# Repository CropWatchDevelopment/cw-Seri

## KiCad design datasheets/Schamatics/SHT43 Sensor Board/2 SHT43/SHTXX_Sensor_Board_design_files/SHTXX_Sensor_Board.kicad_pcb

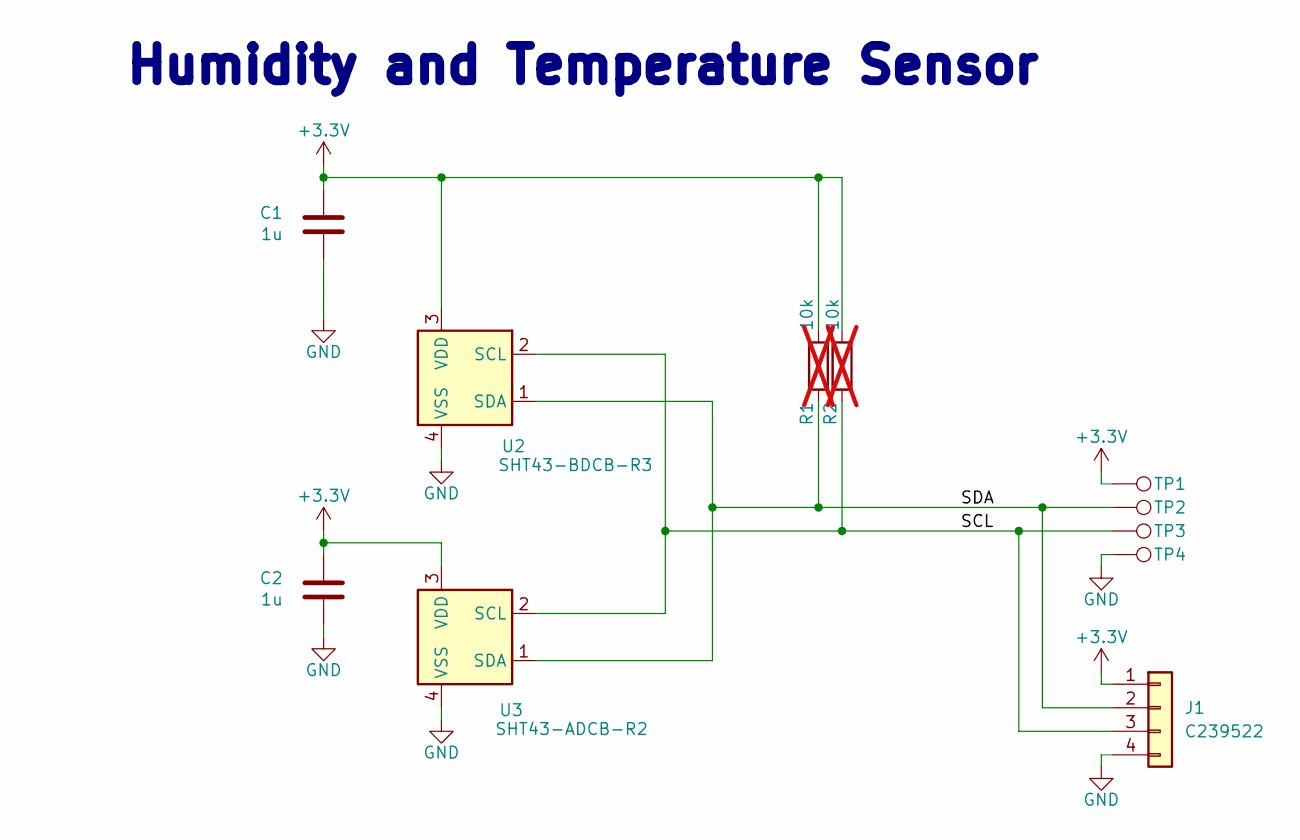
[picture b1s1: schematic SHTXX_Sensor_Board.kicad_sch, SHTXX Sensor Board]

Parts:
C1, C2: 1u; C_0402_1005Metric; Voltage Rating 10V; MPN CL05A105KP5NNNC; LCSC Part # CL05A105KP5NNNC
J1: C239522; SM04B-SRSS-TB_LFSN_; MPN A1002WR-S-4P; LCSC Part # C239522
R1, R2: 10k; R_0402_1005Metric; MPN AC0402FR-0710KL; not fitted
TP1, TP2, TP3, TP4: TestPoint; TestPoint_Pad_D2.0mm
U2: SHT43-BDCB-R3; Sensirion_DFN-4_1.5x1.5mm_P0.8mm_SHT4x_NoCentralPad
U3: SHT43-ADCB-R2; Sensirion_DFN-4_1.5x1.5mm_P0.8mm_SHT4x_NoCentralPad

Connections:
+3.3V: C1.1, C2.1, J1.1, R1.2, R2.2, TP1.1, U2.3 (VDD), U3.3 (VDD)
/SCL: J1.3, R2.1, TP3.1, U2.2 (SCL), U3.2 (SCL)
/SDA: J1.2, R1.1, TP2.1, U2.1 (SDA), U3.1 (SDA)
GND: C1.2, C2.2, J1.4, TP4.1, U2.4 (VSS), U3.4 (VSS)

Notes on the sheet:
Humidity and Temperature Sensor

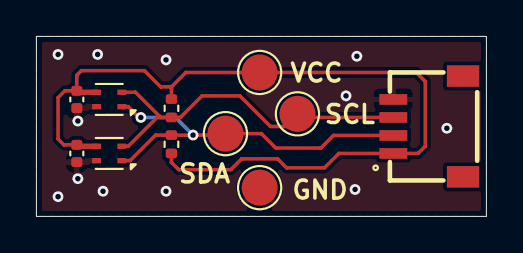
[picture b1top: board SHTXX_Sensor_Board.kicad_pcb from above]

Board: 2 copper layers, 25.0 x 10.0 mm, 11 parts (0 on the bottom side), 4 nets.

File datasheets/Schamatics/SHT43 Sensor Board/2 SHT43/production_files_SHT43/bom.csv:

Designator,Footprint,Quantity,Value,LCSC Part #
"C1, C2",0402,2,1u,CL05A105KP5NNNC 
J1,SM04B-SRSS-TB_LFSN_,1,C239522,C239522
U2,Sensirion_DFN-4_1.5x1.5mm_P0.8mm_SHT4x_NoCentralPad,1,SHT43-BDCB-R3,
U3,Sensirion_DFN-4_1.5x1.5mm_P0.8mm_SHT4x_NoCentralPad,1,SHT43-ADCB-R2,

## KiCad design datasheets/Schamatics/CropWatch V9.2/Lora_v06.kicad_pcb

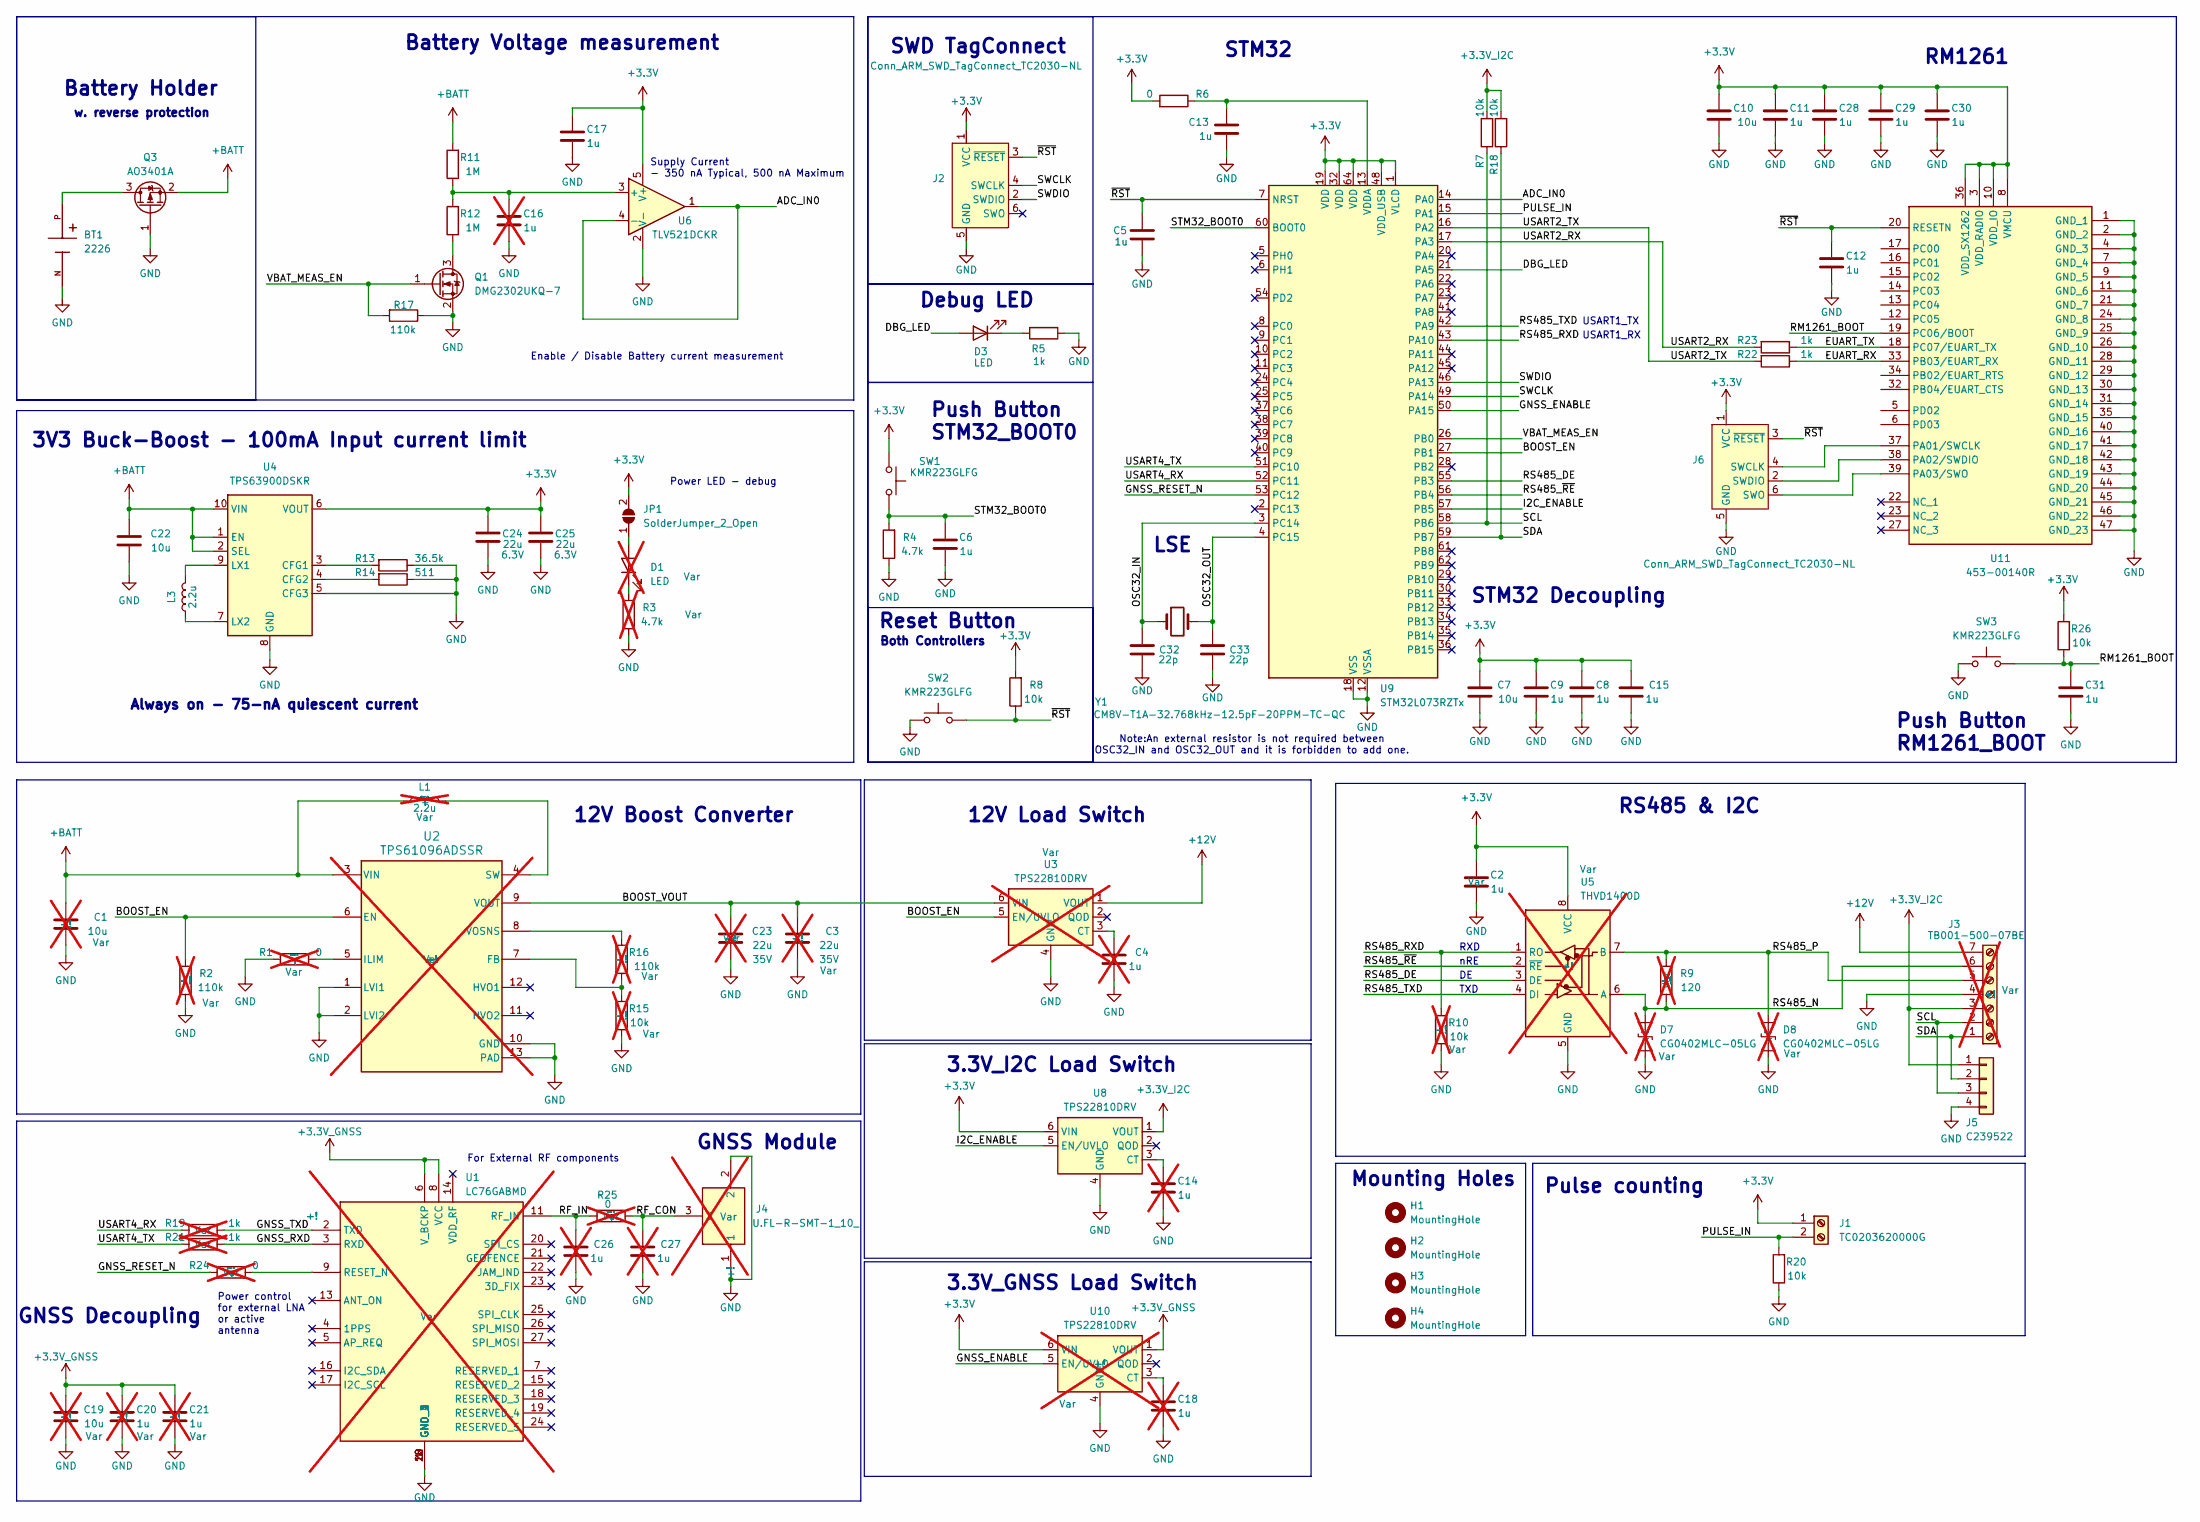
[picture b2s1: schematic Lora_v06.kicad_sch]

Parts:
BT1: 2226; BAT_2226; PARTREV 6.22.07
C1, C19: 10u; C_0603_1608Metric; Voltage Rating 10V; MPN GRM188R61A106ME69J; not fitted
C2, C5, C6, C8, C9, C11, C12, C13, C15, C17, C28, C29, C30, C31: 1u; C_0402_1005Metric; Voltage Rating 10V; MPN CL05A105KP5NNNC
C3, C23: 22u; C_0805_2012Metric; Voltage Rating 35V; MPN C2012X5R1V226M125AC; not fitted
C4, C14, C16, C18, C20, C21, C26, C27: 1u; C_0402_1005Metric; Voltage Rating 10V; MPN CL05A105KP5NNNC; not fitted
C7, C10, C22: 10u; C_0603_1608Metric; Voltage Rating 10V; MPN GRM188R61A106ME69J
C24, C25: 22u; C_0603_1608Metric; Voltage Rating 6.3V; MPN GRM188R60J226MEA0J
C32, C33: 22p; C_0402_1005Metric; Voltage Rating 50V; MPN GRM1555C1H220JA01J
D1: LED; LED_0402_1005Metric; MPN QBLP595-IG; not fitted
D3: LED; LED_0402_1005Metric; MPN QBLP595-IG
D7, D8: CG0402MLC-05LG; D_0402_1005Metric; MPN CG0402MLC-05LG; not fitted
H1, H2, H3, H4: MountingHole; MountingHole_4.3mm_M4
J1: TC0203620000G; MPN TC0203620000G
J2, J6: Conn_ARM_SWD_TagConnect_TC2030-NL; Tag-Connect_TC2030-IDC-NL_2x03_P1.27mm_Vertical
J3: TB001-500-07BE; CUI_TB001-500-07BE; MPN TB001-500-07BE; not fitted
J4: U.FL-R-SMT-1_10_; Mouser Part Number 798-U.FL-R-SMT-110; not fitted
J5: C239522; SM04B-SRSS-TB_LFSN_; MPN A1002WR-S-4P; LCSC Part # C239522
JP1: SolderJumper_2_Open; SolderJumper-2_P1.3mm_Open_RoundedPad1.0x1.5mm
L1: 2.2u; L_0805_2012Metric; MPN LQM21PN2R2MGHL; not fitted
L3: 2.2u; L_0805_2012Metric; MPN LQM21PN2R2MGHL
Q1: DMG2302UKQ-7; SOT-23; MPN DMG2302UKQ-7
Q3: AO3401A; SOT-23; MPN AO3401A
R1, R24, R25: 0; R_0402_1005Metric; MPN RC0402FR-070RL; not fitted
R2, R16: 110k; R_0402_1005Metric; MPN RC0402FR-07110KL; not fitted
R3: 4.7k; R_0402_1005Metric; MPN CRGCQ0402F4K7; not fitted
R4: 4.7k; R_0402_1005Metric; MPN CRGCQ0402F4K7
R5, R22, R23: 1k; R_0402_1005Metric; MPN WR04X1001FTL
R6: 0; R_0402_1005Metric; MPN RC0402FR-070RL
R7, R8, R18, R20, R26: 10k; R_0402_1005Metric; MPN AC0402FR-0710KL
R9: 120; R_0402_1005Metric; MPN RC0402FR-07120RL; not fitted
R10, R15: 10k; R_0402_1005Metric; MPN AC0402FR-0710KL; not fitted
R11, R12: 1M; R_0402_1005Metric; MPN CRGCQ0402F1M0
R13: 36.5k; R_0402_1005Metric; MPN RC0402FR-0736K5L
R14: 511; R_0402_1005Metric; MPN RC0402FR-07511RL
R17: 110k; R_0402_1005Metric; MPN RC0402FR-07110KL
R19, R21: 1k; R_0402_1005Metric; MPN WR04X1001FTL; not fitted
SW1, SW2, SW3: KMR223GLFG; SW_Push_1P1T-SH_NO_CK_KMR2xxG; MPN KMR223GLFG
U1: LC76GABMD; Mouser Part Number 277-LC76GABMD; not fitted
U2: TPS61096ADSSR; DSS0012A; MPN TPS61096ADSSR; not fitted
U3, U10: TPS22810DRV; WSON-6-1EP_2x2mm_P0.65mm_EP1x1.6mm; MPN TPS22810DRVR; not fitted
U4: TPS63900DSKR; WSON-10-1EP_2.5x2.5mm_P0.5mm_EP1.2x2mm_ThermalVias; MPN TPS63900DSKR
U5: THVD1400D; SOIC-8_3.9x4.9mm_P1.27mm; MPN THVD1400DR; not fitted
U6: TLV521DCKR; SOT65P210X110-5N; MPN TLV521DCKR
U8: TPS22810DRV; WSON-6-1EP_2x2mm_P0.65mm_EP1x1.6mm; MPN TPS22810DRVR
U9: STM32L073RZTx; LQFP-64_10x10mm_P0.5mm; MPN STM32L073RZT6
U11: 453-00140R; 45300140R; Mouser Part Number 239-453-00140R
Y1: CM8V-T1A-32.768kHz-12.5pF-20PPM-TC-QC; CM8V32768TA020125

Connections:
+3.3V: C2.1, C7.1, C8.1, C9.1, C10.1, C11.1, C15.1, C17.1, C24.1, C25.1, C28.1, C29.1, C30.1, J1.1, J2.1 (VCC), J6.1 (VCC), JP1.2 (B), R6.2, R8.2, R26.2, SW1.1, U4.6 (VOUT), U5.8 (VCC), U6.5 (V+), U8.6 (VIN), U9.1 (VLCD), U9.19 (VDD), U9.32 (VDD), U9.48 (VDD_USB), U9.64 (VDD), U10.6 (VIN), U11.3 (VDD_RADIO), U11.8 (VMCU), U11.10 (VDD_IO), U11.36 (VDD_SX1262)
+3.3V_GNSS: C19.1, C20.1, C21.1, U1.6 (V_BCKP), U1.8 (VCC), U10.1 (VOUT)
+3.3V_I2C: J3.3, J5.1, R7.2, R18.2, U8.1 (VOUT)
+12V: J3.7, U3.1 (VOUT)
+BATT: C1.1, C22.1, L1.1, Q3.2 (S), R11.2, U2.3 (VIN), U4.1 (EN), U4.2 (SEL), U4.10 (VIN)
/ADC_IN0: U6.1, U6.4 (-), U9.14 (PA0)
/BOOST_EN: R2.2, U2.6 (EN), U3.5 (EN/UVLO), U9.27 (PB1)
/BOOST_VOUT: C3.1, C23.1, U2.9 (VOUT), U3.6 (VIN)
/DBG_LED: D3.2 (A), U9.21 (PA5)
/EUART_RX: R22.1, U11.33 (PB03/EUART_RX)
/EUART_TX: R23.1, U11.18 (PC07/EUART_TX)
/GNSS_ENABLE: U9.50 (PA15), U10.5 (EN/UVLO)
/GNSS_RESET_N: R24.1, U9.53 (PC12)
/GNSS_RXD: R21.1, U1.3 (RXD)
/GNSS_TXD: R19.1, U1.2 (TXD)
/I2C_ENABLE: U8.5 (EN/UVLO), U9.57 (PB5)
/OSC32_IN: C32.1, U9.3 (PC14), Y1.1
/OSC32_OUT: C33.1, U9.4 (PC15), Y1.2
/PULSE_IN: J1.2, R20.2, U9.15 (PA1)
/RF_CON: C27.1, J4.3, R25.2
/RF_IN: C26.1, R25.1, U1.11 (RF_IN)
/RM1261_BOOT: C31.1, R26.1, SW3.2, U11.19 (PC06/BOOT)
/RS485_DE: U5.3 (DE), U9.55 (PB3)
/RS485_N: D7.2 (A2), J3.6, R9.1, U5.6 (A)
/RS485_P: D8.2 (A2), J3.5, R9.2, U5.7 (B)
/RS485_RXD: R10.2, U5.1 (RO), U9.43 (PA10)
/RS485_TXD: U5.4 (DI), U9.42 (PA9)
/RS485_~RE: U5.2 (~RE), U9.56 (PB4)
/SCL: J3.2, J5.3, R7.1, U9.58 (PB6)
/SDA: J3.1, J5.2, R18.1, U9.59 (PB7)
/STM32_BOOT0: C6.1, R4.2, SW1.2, U9.60 (BOOT0)
/SWCLK: J2.4 (SWCLK), U9.49 (PA14)
/SWDIO: J2.2 (SWDIO), U9.46 (PA13)
/USART2_RX: R23.2, U9.17 (PA3)
/USART2_TX: R22.2, U9.16 (PA2)
/USART4_RX: R19.2, U9.52 (PC11)
/USART4_TX: R21.2, U9.51 (PC10)
/VBAT_MEAS_EN: Q1.1 (G), R17.2, U9.26 (PB0)
/~RST: C5.1, C12.1, J2.3 (~RESET), J6.3 (~RESET), R8.1, SW2.2, U9.7 (NRST), U11.20 (RESETN)
GND: BT1.N, C1.2, C2.2, C3.2, C4.2, C5.2, C6.2, C7.2, C8.2, C9.2, C10.2, C11.2, C12.2, C13.2, C14.2, C15.2, C16.2, C17.2, C18.2, C19.2, C20.2, C21.2, C22.2, C23.2, C24.2, C25.2, C26.2, C27.2, C28.2, C29.2, C30.2, C31.2, C32.2, C33.2, D7.1 (A1), D8.1 (A1), J2.5 (GND), J3.4, J4.1, J4.2, J5.4, J6.5 (GND), Q1.2 (S), Q3.1 (G), R1.1, R2.1, R3.1, R4.1, R5.1, R10.1, R13.1, R14.1, R15.1, R17.1, R20.1, SW2.1, SW3.1, U1.1 (GND_1), U1.10 (GND_2), U1.12 (GND_3), U1.28 (GND_4), U2.1 (LVI1), U2.2 (LVI2), U2.10 (GND), U2.13 (PAD), U3.4 (GND), U3.7 (GND), U4.5 (CFG3), U4.8 (GND), U4.11 (GND), U5.5 (GND), U6.2 (V-), U8.4 (GND), U8.7 (GND), U9.12 (VSSA), U9.18 (VSS), U9.31 (VSS), U9.47 (VSS), U9.63 (VSS), U10.4 (GND), U10.7 (GND), U11.1 (GND_1), U11.2 (GND_2), U11.4 (GND_3), U11.7 (GND_4), U11.9 (GND_5), U11.11 (GND_6), U11.21 (GND_7), U11.24 (GND_8), U11.25 (GND_9), U11.26 (GND_10), U11.28 (GND_11), U11.29 (GND_12), U11.30 (GND_13), U11.31 (GND_14), U11.35 (GND_15), U11.40 (GND_16), U11.41 (GND_17), U11.42 (GND_18), U11.43 (GND_19), U11.44 (GND_20), U11.45 (GND_21), U11.46 (GND_22), U11.47 (GND_23)
unnamed: D1.2 (A), JP1.1 (A)
unnamed: D1.1 (K), R3.2
unnamed: D3.1 (K), R5.2
unnamed: J6.4 (SWCLK), U11.37 (PA01/SWCLK)
unnamed: J6.2 (SWDIO), U11.38 (PA02/SWDIO)
unnamed: J6.6 (SWO), U11.39 (PA03/SWO)
unnamed: Q1.3 (D), R12.1
unnamed: BT1.P, Q3.3 (D)
unnamed: R24.2, U1.9 (RESET_N)
unnamed: R15.2, R16.1, U2.7 (FB)
unnamed: R1.2, U2.5 (ILIM)
unnamed: L1.2, U2.4 (SW)
unnamed: R16.2, U2.8 (VOSNS)
unnamed: C4.1, U3.3 (CT)
unnamed: R13.2, U4.3 (CFG1)
unnamed: R14.2, U4.4 (CFG2)
unnamed: L3.2, U4.9 (LX1)
unnamed: L3.1, U4.7 (LX2)
unnamed: C16.1, R11.1, R12.2, U6.3 (+)
unnamed: C14.1, U8.3 (CT)
unnamed: C13.1, R6.1, U9.13 (VDDA)
unnamed: C18.1, U10.3 (CT)

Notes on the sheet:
STM32
3V3 Buck-Boost - 100mA Input current limit
3.3V_GNSS Load Switch
Push Button STM32_BOOT0
LSE
RM1261
STM32 Decoupling
Push Button RM1261_BOOT
RS485 & I2C
Supply Current - 350 nA Typical, 500 nA Maximum
12V Boost Converter
Both Controllers
SWD TagConnect
Pulse counting
Battery Holder
12V Load Switch
3.3V_I2C Load Switch
Power control for external LNA or active antenna
w. reverse protection
USART1_RX
Enable / Disable Battery current measurement
nRE
TXD
RXD
Always on - 75-nA quiescent current
Battery Voltage measurement
GNSS Decoupling
Debug LED
GNSS Module
Note:An external resistor is not required between OSC32_IN and OSC32_OUT and it is forbidden to add one.
For External RF components
Mounting Holes
Reset Button
USART1_TX
Power LED - debug

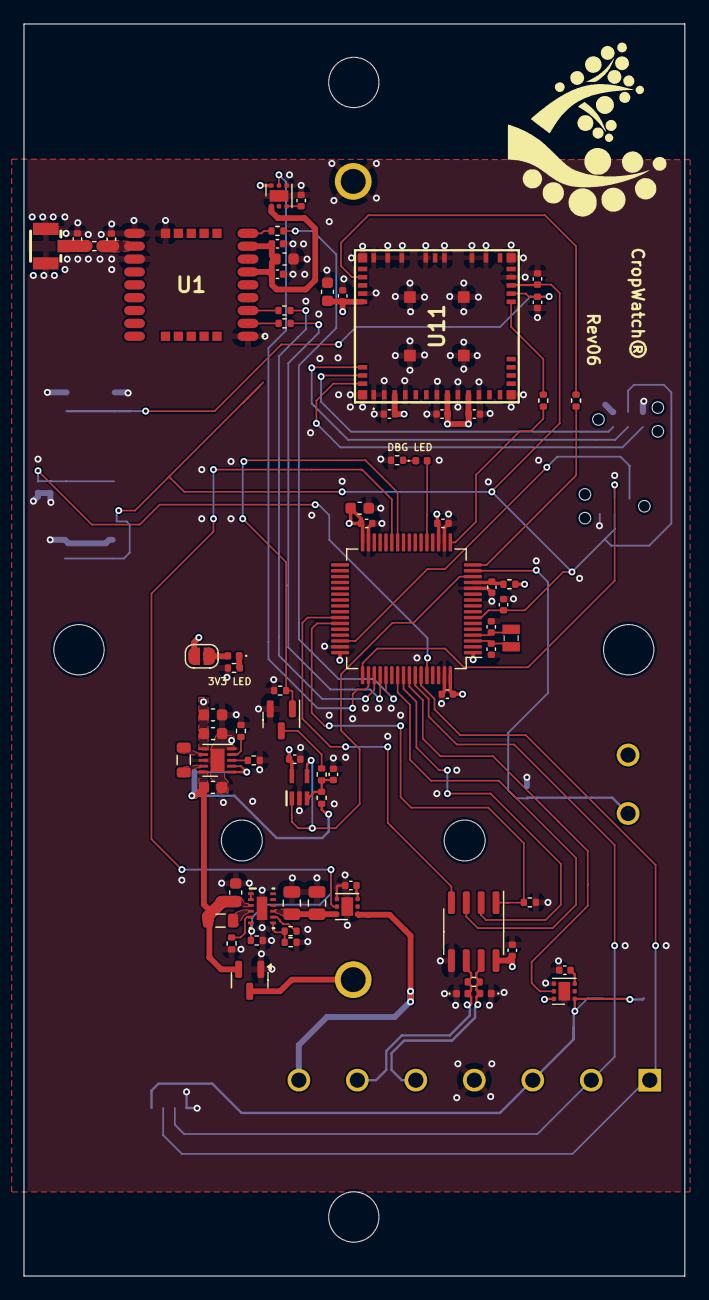
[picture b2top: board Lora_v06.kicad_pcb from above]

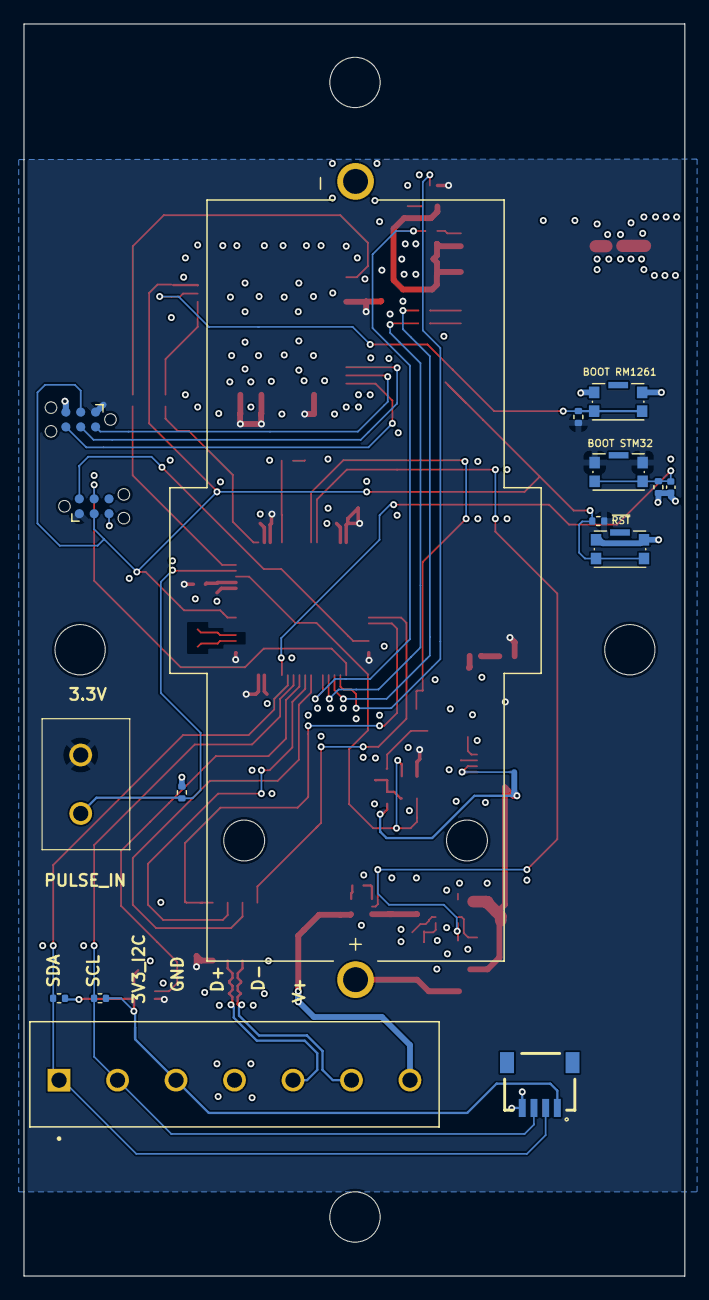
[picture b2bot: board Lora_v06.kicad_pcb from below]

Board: 4 copper layers, 56.5 x 107.0 mm, 93 parts (16 on the bottom side), 62 nets.

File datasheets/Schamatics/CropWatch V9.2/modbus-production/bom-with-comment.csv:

Designator,Footprint,Quantity,Value,LCSC Part #,Comment
"C1, C10, C19, C22, C7",603,5,10u,C109453,GRM188R61A106ME69J
"C11, C12, C13, C15, C17, C2, C20, C21, C28, C29, C30, C31, C5, C6, C8, C9",402,16,1u,C14445,CL05A105KP5NNNC
"C23, C3",805,2,22u,C2012X5R1V226M125AC,C2012X5R1V226M125AC
"C24, C25",603,2,22u,C426040,GRM188R60J226MEA0J
"C32, C33",402,2,22p,GRM1555C1H220JA01J,GRM1555C1H220JA01J
"D1, D3",402,2,LED,QBLP595-IG,QBLP595-IG
"D7, D8",402,2,CG0402MLC-05LG,CG0402MLC-05LG,CG0402MLC-05LG
J1,TC0203620000G,1,TC0203620000G,TC0203620000G,TC0203620000G
J3,CUI_TB001-500-07BE,1,TB001-500-07BE,TB001-500-07BE,TB001-500-07BE
J4,U.FL-R-SMT-1_10_,1,U.FL-R-SMT-1_10_,U.FL-R-SMT-1(10),U.FL-R-SMT-1(10)
J5,SM04B-SRSS-TB_LFSN_,1,C239522,C239522,C239522
"L1, L3",805,2,2.2u,C341781,LQM21PN2R2MGHL
Q1,SOT-23,1,DMG2302UKQ-7,C5224573,DMG2302UKQ-7
Q3,SOT-23,1,AO3401A,C15127,AO3401A
"R1, R24, R25, R6",402,4,0,C106231,RC0402FR-070RL
"R10, R15, R18, R20, R26, R7, R8",402,7,10k,C144807,AC0402FR-0710KL
"R11, R12",402,2,1M,C26083,CRGCQ0402F1M0
R13,402,1,36.5k,C15011,RC0402FR-0736K5L
R14,402,1,511,C25124,RC0402FR-07511RL
"R16, R17, R2",402,3,110k,C138065,RC0402FR-07110KL
"R19, R21, R22, R23, R5",402,5,1k,C163815,WR04X1001FTL
"R3, R4",402,2,4.7k,C25900,CRGCQ0402F4K7
R9,402,1,120,RC0402FR-07120RL,RC0402FR-07120RL
"SW1, SW2, SW3",SW_Push_1P1T-SH_NO_CK_KMR2xxG,3,KMR223GLFG,C221678,KMR223GLFG
U1,LC76GABMD,1,LC76GABMD,LC76GABMD,LC76GABMD
"U10, U3, U8",WSON-6-1EP_2x2mm_P0.65mm_EP1x1.6mm,3,TPS22810DRV,TPS22810DRVR,TPS22810DRVR
U11,45300140R,1,453-00140R,C34819641,453-00140R
U2,DSS0012A,1,TPS61096ADSSR,TPS61096ADSSR,TPS61096ADSSR
U4,WSON-10-1EP_2.5x2.5mm_P0.5mm_EP1.2x2mm_ThermalVias,1,TPS63900DSKR,C1518762,TPS63900DSKR
U5,SOIC-8_3.9x4.9mm_P1.27mm,1,THVD1400D,THVD1400DR,THVD1400DR
U6,SOT65P210X110-5N,1,TLV521DCKR,C655085,TLV521DCKR
U9,LQFP-64_10x10mm_P0.5mm,1,STM32L073RZTx,STM32L073RZT6,STM32L073RZT6
Y1,CM8V32768TA020125,1,CM8V-T1A-32.768kHz-12.5pF-20PPM-TC-QC,,

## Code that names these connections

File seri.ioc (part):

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Mcu.Name=STM32L073R(B-Z)Tx
Mcu.Package=LQFP64
Mcu.UserName=STM32L073RZTx
PA0.GPIOParameters=GPIO_Label
PA0.GPIO_Label=ADC_IN0
PA0.Mode=IN0
PA0.Signal=ADC_IN0
PA2.GPIOParameters=GPIO_Label
PA2.GPIO_Label=LoRaWAN_TX
PA2.Mode=Asynchronous
PA2.Signal=USART2_TX
PA3.GPIOParameters=GPIO_Label
PA3.GPIO_Label=LoRaWAN_RX
PA3.Mode=Asynchronous
PA3.Signal=USART2_RX
PA5.GPIOParameters=GPIO_Label
PA5.GPIO_Label=DBG_LED
PA5.Signal=GPIO_Output
PB5.GPIOParameters=GPIO_Label
PB5.GPIO_Label=I2C_ENABLE
PB5.Signal=GPIO_Output
PB6.Mode=I2C
PB6.Signal=I2C1_SCL
PB7.Mode=I2C
PB7.Signal=I2C1_SDA
PC13.Mode=SYS_WakeUp1
PC13.Signal=SYS_WKUP2
PC14-OSC32_IN.Mode=LSE-External-Oscillator
PC14-OSC32_IN.Signal=RCC_OSC32_IN
PC15-OSC32_OUT.Mode=LSE-External-Oscillator
PC15-OSC32_OUT.Signal=RCC_OSC32_OUT
RCC.HSE_VALUE=8000000
RCC.SYSCLKFreq_VALUE=16000000
RCC.SYSCLKSource=RCC_SYSCLKSOURCE_HSI
board=custom

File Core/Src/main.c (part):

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      }

      // Get I2C Data
      HAL_GPIO_WritePin(I2C_ENABLE_GPIO_Port, I2C_ENABLE_Pin, GPIO_PIN_SET);
      HAL_Delay(1000); // sensor power-up and stabilization
      scan_i2c_bus();
      int i2c_success = sensor_init_and_read();
      HAL_GPIO_WritePin(I2C_ENABLE_GPIO_Port, I2C_ENABLE_Pin, GPIO_PIN_RESET);

      // Format data and send
      uint8_t payload[6] = {0};
      if (i2c_success == 0)
      {
        HAL_GPIO_WritePin(GPIOB, VBAT_MEAS_EN_Pin | I2C_ENABLE_Pin, GPIO_PIN_SET);
        HAL_Delay(300);
        int aproxBatteryTemp_c = ((calculated_temp_1 - 55) / 10);
        uint8_t battery = vbat_measure_and_encode(&hadc, ADC_CHANNEL_0, aproxBatteryTemp_c, /*external_power_present=*/false);
        HAL_GPIO_WritePin(GPIOB, VBAT_MEAS_EN_Pin | I2C_ENABLE_Pin, GPIO_PIN_RESET);
        lorawan_set_battery_level(&huart2, battery);

        if (has_soil_sensor)
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  __HAL_RCC_GPIOB_CLK_ENABLE();

  /*Configure GPIO pin Output Level */
  HAL_GPIO_WritePin(DBG_LED_GPIO_Port, DBG_LED_Pin, GPIO_PIN_RESET);

  /*Configure GPIO pin Output Level */
  HAL_GPIO_WritePin(GPIOB, VBAT_MEAS_EN_Pin|I2C_ENABLE_Pin, GPIO_PIN_RESET);

  /*Configure GPIO pin : DBG_LED_Pin */
  GPIO_InitStruct.Pin = DBG_LED_Pin;
  GPIO_InitStruct.Mode = GPIO_MODE_OUTPUT_PP;
  GPIO_InitStruct.Pull = GPIO_NOPULL;
  GPIO_InitStruct.Speed = GPIO_SPEED_FREQ_LOW;
  HAL_GPIO_Init(DBG_LED_GPIO_Port, &GPIO_InitStruct);

  /*Configure GPIO pins : VBAT_MEAS_EN_Pin I2C_ENABLE_Pin */
  GPIO_InitStruct.Pin = VBAT_MEAS_EN_Pin|I2C_ENABLE_Pin;
  GPIO_InitStruct.Mode = GPIO_MODE_OUTPUT_PP;
  GPIO_InitStruct.Pull = GPIO_NOPULL;
  GPIO_InitStruct.Speed = GPIO_SPEED_FREQ_LOW;
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  GPIO_InitStruct.Mode = GPIO_MODE_ANALOG;
  GPIO_InitStruct.Pull = GPIO_NOPULL;

  /* Configure GPIOA pins (except UART pins PA2, PA3 and PA9, PA10) */
  GPIO_InitStruct.Pin = GPIO_PIN_0 | GPIO_PIN_1 | GPIO_PIN_4 | GPIO_PIN_5 |
                        GPIO_PIN_6 | GPIO_PIN_7 | GPIO_PIN_8 | GPIO_PIN_11 |
                        GPIO_PIN_12 | GPIO_PIN_13 | GPIO_PIN_14 | GPIO_PIN_15;
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  GPIO_InitStruct.Pin = GPIO_PIN_All;
  HAL_GPIO_Init(GPIOB, &GPIO_InitStruct);

  /* Configure GPIOC pins (except PC14, PC15 for LSE crystal) */
  GPIO_InitStruct.Pin = GPIO_PIN_0 | GPIO_PIN_1 | GPIO_PIN_2 | GPIO_PIN_3 |
                        GPIO_PIN_4 | GPIO_PIN_5 | GPIO_PIN_6 | GPIO_PIN_7 |
                        GPIO_PIN_8 | GPIO_PIN_9 | GPIO_PIN_10 | GPIO_PIN_11 |
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
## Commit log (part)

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2025-08-27 10 minutes, deep sleep all working!
2025-08-29 rtc working
2025-08-29 clean the repo from file which shall not be tracked
2025-08-29 further clean-up of repo from files which shall not be tracked
2025-08-29 started converting polling-based uart to interrupt-based uart
2025-08-30 adding battery check, re-adding in connection check
2025-08-30 working temp/humdiity!
2025-08-31 working with sensor error check
2025-09-01 test point, RC1 release
2025-09-01 added basic infrastructure for interrupt-based uart tx functionality and API
2025-09-01 added essential documetation
2025-09-01 updates for TTN Decoder and how the SHT4x Temp reading is being processed
2025-09-01 adding unit tests for TTN-Decoder.js
2025-09-01 adding git ignore
2025-09-02 builds with no errors
2025-09-03 - added a successfully-compiled API of interrupt-based UARTs.
2025-09-03 adding uris .gitignore file
2025-09-03 removing junk file
2025-09-03 adding test branch
2025-09-03 Clearning up the repo from generated files which shall not be tracked.
2025-09-03 - updated USART1 and USART2 source clocks to HSI 16 (Mhz)
2025-09-04 - added some debug info
2025-09-04 - updated the expected length of a received message for the test - added some further handling at the rx-interrupt
2025-09-04 updated baud
2025-09-04 - some minor fix-ups - reduction of baud rate to 38400 from 115200
2025-09-04 - removed a debug-related file from the files being tracked in the repo.
2025-09-04 -remove a local debug-related file from being tracked
2025-09-04 - tried to fix some merge collisions
2025-09-04 - added (back) missing USART interrupt-handlers (ISRs)
2025-09-04 - removed additional files from being tracked in the repo
2025-09-04 - allow multiple responses from the LORA chip to accumulate in the rx_buffer.
2025-09-06 - implement a header / code template into the files.
2025-09-09 - introducing a new AT-command skeleton and extensible API for the RM126x LoRaWAN chip.
2025-09-09 - another file to remove from the repo.
2025-09-09 .sh program should be working will test soon
2025-09-10 release 1
2025-09-11 fix to humidity and decoder
2025-09-13 - added two file extensions to ignore in the repo
2025-09-13 - further clean-up of the repo
2025-09-20 working
2025-10-03 small updates
2025-10-03 safety
2025-10-04 mid-test
2025-10-04 borked
2025-10-14 soil sensor added
2025-10-14 adding in error case on data send
2025-10-15 added restart login if hitting ERROR 14
2025-10-20 - clean-up repo: stopped a long list of debug-related files from being tracked by the repo
2025-10-20 - clean-up repo: stopped another set of debug-related files from being tracked by the repo
2025-10-21 - fix build: > removed duplicate definitions of MX_ functions which were extracted into their own files.
2025-10-21 test
2025-10-21 - RTC clock source configuration: > System clock source is set to MSI (2097 KHz). > LSE is set to drive RTC by default. > CSS Enabled, i.e. hardware detects LSE faults and software (interrupt) replac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
2025-10-21 - added HAL and LL support of the Low-Power timer.
2025-10-22 - set available memory for RTOS to a more realistic value
2025-10-22 - removed support of Dynamic memory allocations in FreeRTOS
2025-10-22 moved crystal setting from LOW (bad) to Medium Low (better)
2025-10-22 preparing some more OS-infrastructure for development / debugging of the application tasks..
2025-10-22 some tweaking of FreeRTOS configurations, low-power-timer and uarts.
2025-10-22 Added a basic error-logging mechanism and an example of how it would be used in an OS-task.
2025-10-23 update LSE_DRIVE level to Medium-High (from Low)
2025-10-23 started some basic os-based application-code
2025-10-23 added some error types
2025-10-23 clearing code which isn't required at this point
2025-10-25 replaced the error-recording mechanism with a basic logger mechanism which can log errors as well as positive progress.
2025-10-25 - build: fix code using the new logger mechanism.
2025-10-25 Set the main clock source back to ~2MHz MSI with regulator voltage increased to SCALE3 (from SCALE1) and RCC_PWR_CLOCK enabled and done at the end of clocks configuration. HSI is ON, for the purpose 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
2025-10-25 optimizing the performance of FreeRTOS in the currently project.
    In addition, extracted the os-related functionality into a separate file to avoid unecessary changes when the .ioc changes and new code is re-gererated.
2025-10-27 stop tracking *.launch files
2025-10-27 disable some old code from the program.
2025-10-27 added a validation check to the creation of an os-queue.
2025-10-29 adding datasheets
2025-10-30 impr. - have done some optimization around the sensirion temperature and humidity sensor drivers and utilities.
2025-10-30 file changes
2025-11-02 feat: relocated logger module into Infrastructure as well as extended it.
2025-11-03 build: removing non-required os-functionality from the build
2025-11-03 style: some minor non-important updates: typos, formatting, etc.
2025-11-03 refactor: updated the calls to Logger APIs
2025-11-03 refactor: some logical updates and improved formatting related to the temperature and humidity sensors of Sensirion.
2025-11-13 ai seemingly fixed stuff
2025-11-14 adding fallback from LSE to LSI
2025-11-14 updating git ignore and removing node_modules
2025-11-14 removing node stuff
2025-11-14 keeping node_modules gone
2025-11-14 clean-up: stopped tracking (and removed) files with the following extensions: .d, .o, .su, .cyclo, .map
2025-11-14 feature: added a fallback mechanism from using LSE to using LSI in case the CSS detects a fault in the LSE clock source. In addition, handled NMI and Hard_Fault interrupts to not wait on a while(1) f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
2025-11-16 feature: the reason for the very last reset performed by the MCU is now available via the API: Read_Reset_Reason()
2025-12-09 working rejoin if STM32 resets
2025-12-10 Stop tracking Release directory
2025-12-10 removing release directory from git
2025-12-10 created LLM.txt for Ezurio Module
2025-12-10 good
2025-12-21 battery now reads every 100 cycles
2025-12-21 ensure sleep
2025-12-22 adding correct formatter for C/C++
2025-12-22 creating release build in gh
2025-12-23 trying to optimize for power safety
2025-12-29 LSI Trimming working
2025-12-29 LSI trimming using LSE with failover and recover working!!!!
2025-12-29 nearing perfection
2025-12-30 temp working seemingly
2025-12-30 adding in WDG
2025-12-30 forcing LSE to always use the highest drive capability
2025-12-31 removing hault possability
2026-01-02 seemingly working
2026-01-02 tested with cold spray, reset works well
2026-01-02 fixed problem with .ioc
2026-01-02 removed un-used variable and ensured that updating .ioc file does not break code
2026-01-07 updating TTI-Decoder
2026-01-30 soil sensor working, and early send, sends
2026-02-06 Initial plan
2026-02-06 Fix critical bugs that can halt STM32L0 program execution
    1. SystemClock_Config: respect LSI failover state after STOP wakeup
    to prevent reset loop when LSE crystal fails
    2. rtc_switch_to_lsi_failover: use cycle-count loop instead of
    HAL_GetTick() to prevent infinite hang when called from NMI
    context with SysTick suspended
    3. Remove unguarded wakeup_counter=0 race condition that could
2026-02-06 Extract LSI timeout magic number to named constant per review
2026-02-06 Remove accidentally committed CodeQL artifact, add to .gitignore
2026-02-08 Harden STM32L0 sleep/wake failover to prevent execution stalls
2026-02-08 Fix critical bugs: sleep/wake race condition, UART buffer overflow in join() and LoRaWAN_SendHex()
    1. EnterDeepSleepMode: Added __disable_irq() before clearing alarm flags and
    checking g_alarm_fired, preventing the race where the alarm fires between
    arming and WFI. Uses PRIMASK+WFI pattern (ARM recommended) to ensure WFI
    still wakes on pending interrupts. Added early return if alarm already fired.
    2. join(): Added buffer-full guard before calling HAL_UARTEx_ReceiveToIdle to
    prevent passing size=0 which can cause HardFault on some HAL versions.
2026-02-08 Update comment per code review feedback
2026-02-08 Remove CodeQL artifact and add to .gitignore
2026-02-09 Fix critical bugs that can halt STM32L0 program execution
    Bug 1: SystemClock_Config() LSE failure causes reset loop - add LSI fallback
    Bug 2: UART2 not DeInit'd before clock disable - potential bus fault/HardFault
    Bug 3: configWakeupTime() last-resort calls Error_Handler - avoid MCU reset
    Bug 4: SysTick suspended before configWakeupTime - HAL timeouts hang forever
    Bug 5: NMI handler LSI failover uses HAL_GetTick with SysTick suspended - hangs
    Bug 6: readCount never incremented - battery measurement never executes
2026-02-09 Address code review: improve comments on magic numbers and fix non-ASCII character
2026-02-09 testing at sea
2026-02-09 Fix critical bugs that can halt STM32L0 program execution
    BUG 1: Race condition in EnterDeepSleepMode - alarm flag cleared after arming
    The old code unconditionally cleared ALRAF and EXTI flags before WFI.
    If the alarm fired between rtc_arm_alarm_a() and the flag clear, the
    wake source was erased and WFI would sleep until watchdog reset.
    Fix: check if alarm already fired and skip sleep if so.
    BUG 2: Buffer overflow in join() UART receive loop
2026-02-09 Clear ALRAF and EXTI flags in race-condition guard to prevent tight loop
2026-02-09 Final review - all fixes verified
2026-02-09 Remove accidentally committed CodeQL artifact
2026-02-09 increasing the stack size from 0x400 TO 0x800
2026-02-09 added fix four sleep
2026-02-09 Restored RTC alarm sanity check (prevents stale/corrupt far-future sleep scheduling
2026-02-09 Fix unbounded send-epoch catch-up loop and I2C HAL type mismatch
    Bug #5: Replace unbounded while loop in g_next_send_epoch catch-up
    (main.c:1171) with O(1) arithmetic. A corrupted/stale BKP value
    could cause millions of iterations, starving the watchdog.
    Bug #1/#2: Widen sensirion_i2c_hal_read/write count parameter from
    uint8_t to uint16_t to match callers in sensirion_i2c.c which pass
    uint16_t size values. Prevents silent truncation on larger reads.
2026-02-09 Add overflow and division-by-zero guards to send-epoch catch-up
    Address code review feedback: guard against send_interval_seconds==0
    division and uint32_t multiplication overflow when computing catch-up
    steps for g_next_send_epoch.
2026-02-09 temp
2026-02-11 fixed min stack size issue possibly leading to haults
2026-02-13 removed tiny but possible counter wrap, and removed un-used incrementing variable
2026-02-13 Harden wake diagnostics and fault recovery on memfix
2026-02-14 fix: prevent sleep/wake failure after 3-4 weeks
    Two interacting bugs caused the device to stop waking after weeks:
    1. calendar_add_seconds -> calendar_add_minutes had an integer truncation
    bug on date rollover. When days_to_add was large (stale BKP state after
    watchdog reset), cal->day (uint8_t) could be corrupted, producing an
    invalid RTC alarm date that never matches -> device never wakes.
    Fix: Replace calendar_add_seconds with epoch-based arithmetic using the
2026-02-16 Fix reliability issues: enable IWDG, fix readCount, race conditions, stack size, RTC calendar init
2026-02-16 Fix IWDG timeout comment: ~26s -> ~28s
2026-02-16 Final review - all reliability fixes complete
2026-02-16 Remove CodeQL artifact from repo, add to .gitignore
2026-02-16 Fix calendar year rollover, day/month sanitization, remove unused RAM, fix unsigned suffix
    - Clamp year at 99 instead of wrapping to 0 in calendar_add_minutes()
    to prevent epoch calculation breakage
    - Add day and month sanitization in calendar_add_minutes() to guard
    against corrupt calendar state causing arithmetic underflows
    - Remove unused msgbuf[256] global from sensirion_i2c_hal to save 256
    bytes of scarce RAM on 20KB STM32L073
2026-02-16 seemingly perfect?
2026-03-24 updating latest
2026-04-11 cherry picked the reset-reason discovery feature

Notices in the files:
Core/Src/main.c:
Copyright (c) 2025 STMicroelectronics.
All rights reserved.
This software is licensed under terms that can be found in the LICENSE file
